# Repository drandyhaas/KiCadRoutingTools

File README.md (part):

# KiCad Routing Tools

A fast Rust-accelerated A* autorouter for KiCad PCB files. Compatible with **KiCad 9 and KiCad 10**. Available as both a **KiCad Plugin** with full GUI and a **Command-Line Interface** for scripting and automation.

📊 **[Project metrics](https://drandyhaas.github.io/KiCadRoutingTools/metrics/)** — installs, downloads and traffic, updated daily.

<p align="center">
  
  <br>
  Free and MIT-licensed. Donations cover the ~$500/month of cloud compute and AI development behind it.
  <br>
  Also via <a href="https://github.com/sponsors/drandyhaas">GitHub Sponsors</a> or <a href="https://www.paypal.me/DrAndyHaas">PayPal</a> — see <a href="#support">Support</a>.
</p>

## Contents

- [Support](#support) — donate via Ko-fi, GitHub Sponsors or PayPal
- [Features](#features)
- [Quick Start](#quick-start)
- [KiCad Plugin](#kicad-plugin) — GUI, the **Auto** tab (the Autorouter, AI routing and placement, labels), installation
- [Command-Line Interface](#command-line-interface) — routing, planes, verification
- [Documentation](#documentation) — full guide for every feature
- [Project Structure](#project-structure) & [Module Overview](#module-overview)
- [Performance](#performance)
- [Command Reference](#command-reference) — options per tool (full list: `--help` / [configuration.md](docs/configuration.md))
- [Project metrics](https://drandyhaas.github.io/KiCadRoutingTools/metrics/) — installs, downloads and traffic
- [Requirements](#requirements) · [Limitations](#limitations) · [Contributing](#contributing) · [License](#license)

## Support

KiCadRoutingTools is free and MIT-licensed, and it stays that way — there is no
paid tier, no feature held back, and nothing in this repository is paywalled.

Donations go to what it costs to build and maintain it: about **$500/month** of
cloud computing and AI-assisted development.

The compute is not incidental. Every change to the router is A/B-tested by
replaying a corpus of real open-source boards on rented cores and grading each
one for DRC violations and unconnected nets, and the ~770-file test suite fans
out the same way. It is what stops a change that helps one board from quietly
breaking ten others.

- **[☕ Donate on Ko-fi](https://ko-fi.com/drandyhaas)** — card or PayPal, no account needed.
- **[GitHub Sponsors](https://github.com/sponsors/drandyhaas)** — one-time or monthly, billed with any other projects you sponsor.
- Prefer PayPal directly? **[paypal.me/DrAndyHaas](https://www.paypal.me/DrAndyHaas)** (the sender needs a PayPal account).

A donation buys no priority support and unlocks no features. If you would rather
contribute something worth more than money, route one of your own boards and file
an issue for whatever breaks — see [Contributing](#contributing).

## Features

Fast, grid-based A\* routing with a native Rust core (~10× faster than pure Python): octilinear (H/V/45°) multi-layer routing with automatic vias, and batch routing with incremental obstacle caching. Highlights below link to the full deep-dive docs.

**Core routing**
- Rust-accelerated A\* pathfinding, multi-layer with automatic via insertion
- [Rip-up and reroute](docs/rip-up-reroute.md) — progressive N+1 blocker analysis, ripped-corridor avoidance
- [Net ordering strategies](docs/net-ordering.md) — MPS (crossing-aware), inside-out, original, or bus-first, with MPS layer swaps
- Stub layer switching, vertical track alignment, turn-cost straightening
- Board-edge (Edge.Cuts arcs/cutouts), keep-out rule areas, and auto BGA exclusion zones — see [Configuration](docs/configuration.md)
- Direction-aware stub / BGA / track [proximity penalties](docs/configuration.md)

**Differential pairs** — see [Differential Pairs](docs/differential-pairs.md)
- Pose-based A\* with a Dubins heuristic and adaptive setback angles for orientation-aware centerlines
- Bare-pad, multi-point (3+ terminals), and hybrid (coupled middle + single-ended legs) routing
- Automatic polarity resolution (opt-in pad swaps), U-turn prevention, GND return-via placement
- Electrically-short legs auto-defer to single-ended; per-layer [impedance-controlled](docs/differential-pairs.md) widths

**Power & planes** — see [Plane Routing](docs/route-plane.md) and [Power Nets](docs/power-nets.md)
- [Wider power-net routing](docs/power-nets.md) with automatic neck-down at fine-pitch pads
- Plane pours (pads are welded by the route step, #562) and plane layers several nets share (split round spines routed on the layer) with resistance / max-current reporting
- Disconnected-plane-region repair (region joins + pad taps) and GND return-via placement

**Signal integrity**
- [Length matching](docs/length-matching.md) — trombone meanders, auto DQ/DQS grouping, via-barrel aware
- [Time matching](docs/length-matching.md#time-matching) — propagation delay, microstrip vs stripline
- [Bus routing](docs/bus-routing.md), plus [guide corridors and keep-out zones](docs/configuration.md) drawn on a User layer

**Placement, fanout & optimization**
- [Placement by function](py_placer/placement/README.md): parts sorted into functional groups, one objective annealed (`place_simple.py`) over 12 seeds (6 started scattered, 6 with each group gathered), and a fast route (`route.py --quick 2`) of the 6 the objective rates best to keep the best (`/plan-pcb-placement`)
- [The design brief](docs/design-brief.md) — state what the board is FOR, in a sibling the toolchain reads: which connectors are user-facing, which edge each belongs on and where along it
- [Parts under other parts](docs/floorplan-intent.md#covers-and-heights-what-stands-over-the-board) — part heights read off the 3D models, so a low part may stand under a module or shield can where it fits; a card in its socket (M.2) or a module on a stacking connector is declared in the brief and moves with its connector, admitting only parts known to fit under it
- [Floorplan intent, graded](docs/floorplan-intent.md) — declare where parts belong and check the board against it, so "the render looks fine" stops being a verdict
- BGA / QFN fanout with decoupling-cap placement cleanup, Hungarian target-swap, and schematic sync

**Cleanup & verification** — see [Utilities](docs/utilities.md)
- Post-route copper cleanup reconciled against the connectivity model (no orphaned or ripped-and-not-restored copper), with gap-snap connectors
- **KiCad-oracle reconnect** — routes the exact links KiCad's own DRC reports as unconnected
- Checkers for DRC, connectivity, orphan stubs, copper hygiene (`check_weird.py`), and pad geometry

**Interfaces**
- Full [KiCad plugin GUI](#kicad-plugin) (KiCad 9 & 10) and a scriptable [CLI](#command-line-interface)
- [AI assistance](docs/claude-skills.md) — an **Auto** tab that runs the Autorouter, plans an entire routing workflow or places a board by function, per-field "Ask AI" helpers, and datasheet-driven power / high-speed / diff-pair analysis
- [Board rendering](docs/utilities.md#board-renderer-route_renderpy) — fast geometry PNG renderer (`route_render.py`), placement stills (`render_placement.py`), a board's power components (`render_power.py`), and movies of a routing run (`route_movie.py`, made for every stress run) and of a placement, or the placement skill's whole flow through to the full route (`place_movie.py`)
- [Routing plans as files](docs/claude-skills.md#plans-from-the-command-line) — save/load a whole routing chain as JSON: build one from a recorded command chain (`make_plan.py`), run it headless through the real plugin (`run_plan.py`), or load it in the GUI

## Quick Start

### 1. Get the Code

```bash
# Clone with git
git clone https://github.com/drandyhaas/KiCadRoutingTools.git
cd KiCadRoutingTools
```

Or [download the ZIP](https://github.com/drandyhaas/KiCadRoutingTools/archive/refs/heads/main.zip) and extract it.

Commands here use `python3`. On Windows, use `py -3` (or `python`) if `python3` is not found.

### 2. Install the Rust Router

```bash
python3 build_router.py
```

By default this downloads a prebuilt binary for your OS from the project's
[GitHub Releases](https://github.com/drandyhaas/KiCadRoutingTools/releases) —
**no Rust toolchain required**. Prebuilts are published for:

- Linux x86_64
- macOS arm64 (Apple Silicon)
- macOS x86_64 (Intel)
- Windows x86_64

If a prebuilt isn't available for your platform (e.g. Linux arm64) or the
download fails, the script falls back to building locally with cargo.

#### Building from source (optional)

If you'd rather build locally — or you're on a platform without a prebuilt —
install Rust from [rustup.rs](https://rustup.rs/):

```bash
# macOS / Linux
curl --proto '=https' --tlsv1.2 -sSf https://sh.rustup.rs | sh

# Windows: Download and run rustup-init.exe from https://rustup.rs/
```

After installation, restart your terminal or run `source ~/.cargo/env`, then:

```bash
python3 build_router.py --from-source     # build locally instead of downloading
python3 build_router.py --tag v0.15.0     # download a specific release
python3 build_router.py --clean           # remove all build artifacts
```

### 3. Choose Your Interface

**To route a whole board automatically, use one of two ways** -- and an AI assistant
asked to route a board with this package should do the same:

- `python3 py_router/autoroute.py board.kicad_pcb routed.kicad_pcb` (Option C): no
  agent; it plans the chain from the board's own rules, footprints and nets and runs it.
  The plugin's **Auto › Autorouter** tab runs the same script.
- the `/plan-pcb-routing` skill (Option B): an agent analyzes the board, plans the
  chain step by step with you, and runs it.

**Option A: KiCad Plugin (Recommended for interactive use)**

```bash
# Install the plugin
python3 install_plugin.py

# Then in KiCad: Tools → External Plugins → KiCadRoutingTools
```

**Option B: Claude Code (AI-assisted routing)**

Use [Claude Code](https://claude.ai/claude-code) to analyze your PCB and generate a routing plan:

```
> /plan-pcb-routing kicad_files/my_board.kicad_pcb
```

Claude will:
- Analyze your board structure and identify components needing fanout (BGA/QFN/PGA)
- Detect differential pairs and DDR signals requiring length matching
- Identify power/ground nets and recommend plane vs trace routing
- Assess signal speeds and recommend GND return via placement
- Generate a step-by-step routing plan with explanations
- Run the commands and verify results

Other useful skills:
```
> /find-high-speed-nets kicad_files/my_board.kicad_pcb       # Identify high-speed nets via datasheet lookup
> /analyze-power-nets kicad_files/my_board.kicad_pcb         # Identify power nets and track widths
> /identify-diff-pairs kicad_files/my_board.kicad_pcb        # Find diff pairs by pin function, recommend gap/impedance
> /recommend-stackup kicad_files/my_board.kicad_pcb          # Stackup advice for impedance/time-matching accuracy
> /recommend-plane-mappings kicad_files/my_board.kicad_pcb   # Which nets get planes, on which layers
> /diagnose-routing-failures my_board.kicad_pcb /tmp/route_output.txt  # Root-cause failed routes, get a retry command
> /review-routed-board my_board_routed.kicad_pcb             # Post-route QA: DRC, connectivity, length match, GND vias
> /plan-pcb-placement full kicad_files/my_board.kicad_pcb    # Group, place 12 seeds, fast-route the 6 cheapest, keep the best, route end to end
```

See [Claude Skills](docs/claude-skills.md) for what each skill does and how they fit together.

All of these are also available inside KiCad without leaving the plugin - see [AI assistance in the plugin](#ai-assistance-auto-tab) below. The plugin can run the analysis and routing skills through [opencode](https://opencode.ai) instead of Claude Code (issue #503) - a Backend dropdown on the Auto tab selects the agent CLI, and opencode's `provider/model` strings open the door to other model providers. The placement runs need Claude Code, because they write files and opencode's analysis agent may not. The skills' output contracts are tuned on Claude models; smaller models may follow them less reliably.

**Option C: Command Line -- route a whole board with `autoroute.py`**

```bash
# Route the whole board: planes, fanouts, decap clearance, diff pairs and route
# passes, chosen from the board's own rules, footprints and nets
python3 py_router/autoroute.py my_board.kicad_pcb routed.kicad_pcb

# See its plan first, without running anything
python3 py_router/autoroute.py my_board.kicad_pcb routed.kicad_pcb --dry-run
```

Every step it ran, with its log and board, is in `routed.kicad_pcb.autoroute/`
(`plan.json` there records the chain and each pass's grade), and its last line,
`AUTOROUTE_SUMMARY`, names the shipped step with its open nets and DRC. See
[`autoroute.py`](docs/utilities.md#deterministic-plan-router-autoroutepy). The
plugin's **Auto › Autorouter** tab runs the same script on the open board.

**Option D: A hand-built chain (the manual / expert path)**

When a board needs steps `autoroute.py` does not take -- impedance control, length
matching, keep-away rules, buses, a particular plane map, or a net class that is a
real requirement rather than aspirational -- run the tools yourself, the kind of chain
`/plan-pcb-routing` plans:

```bash
# Optionally place the board first, by its functional groups (see py_placer/placement/README.md)
python3 py_placer/place_simple.py my_board.kicad_pcb placed.kicad_pcb --groups groups.json --intent intent.json

# Pour the planes FIRST (#562): the fanout's plane-drop vias then land on
# real fill, and the route step welds plane pads into it.
python3 py_router/route_planes.py my_board.kicad_pcb poured.kicad_pcb --nets GND --plane-layers B.Cu

# Fan out a BGA, then tidy decoupling caps off the new vias (issue #130)
python3 py_router/bga_fanout.py poured.kicad_pcb -c U1 -o fanned.kicad_pcb --clearance 0.1
python3 py_placer/place_fanout_clearance.py fanned.kicad_pcb capclean.kicad_pcb --clearance 0.1

# Route differential pairs (the output is positional: route_diff's -o is --ordering)
python3 py_router/route_diff.py capclean.kicad_pcb diffed.kicad_pcb --nets "*lvds*"

# Route ALL remaining nets, plane nets included (their widths via --power-nets).
# This step ends with the in-run plane finalize that completes the planes.
python3 py_router/route.py diffed.kicad_pcb routed.kicad_pcb --nets "*" \
    --power-nets GND --power-nets-widths 0.3
```

---

## KiCad Plugin

The plugin provides a full graphical interface for all routing features, running directly within KiCad 9 or 10.

### AI assistance (Auto tab)

With [Claude Code](https://claude.ai/claude-code) or [opencode](https://opencode.ai) installed, the routing dialog gains AI assistance throughout (the plugin spawns the selected agent CLI headless, streams a live transcript, and fills GUI controls from the results). The **Backend** dropdown on the Auto tab picks the CLI: Claude Code runs Anthropic models; opencode takes `provider/model` strings for many providers (including its built-in free tier), with `opencode auth login` adding provider accounts. Both discover the same `.claude/skills/`; opencode runs them under a read-only `pcb-analysis` agent defined in `opencode.json` (the equivalent of the Claude run's read-only tool allowlist). Neither grants a dedicated write tool, though both grant `Bash`, so neither is a sandbox — the allowlist states intent, and `--allowedTools` auto-approves rather than restricts. Both can dispatch a subagent, so an analysis skill can hand its close-out to an independent verifier (#552): the Claude allowlist grants the dispatch tool per run, and the `pcb-analysis` agent grants opencode's `task` tool in `opencode.json`. A caller asking opencode for a tool set naming `Write`/`Edit` is refused rather than silently downgraded.

The tab has two sub-tabs:

- **Routing** - *Plan Routing* runs `/plan-pcb-routing`: the plan fills the parameter fields across the tabs and appears as a checkable step list, which *Run Selected Steps* executes sequentially in-process on the live board with per-step status marks. *Review Routed Board* and *Diagnose Routing Failures* give post-route QA and failure root-causing. Backend, model, and effort selectors control every AI run and persist with the dialog settings (model/effort remembered per backend).
- **Placement** - *Place (AI)* and *Place + Route (AI)* run `/plan-pcb-placement place` / `full` headless into a `krt_placement/` folder beside the board. The tab shows the seed candidates with a preview, a status line read from the run's milestone ledger, and at the end REPORT.md; *Apply Result to Board* moves the open board's parts to the result's poses and locks (and, after *Place + Route*, its routed copper). These two need Claude Code. *Beautify Labels* (no AI) tidies the reference-designator silkscreen (`py_placer/beautify_labels.py`).
- **Save / Load a plan** - *Save…* writes the generated step list to a JSON file; *Load…* reads one back and runs it with **no Claude call** — handy for replaying a workflow that worked on another board. A recorded command chain converts to a loadable plan too (`python3 py_router/make_plan.py <run dir>`; see [Plans from the command line](docs/claude-skills.md#plans-from-the-command-line)).
- **Per-field "Ask AI" buttons** - power nets/widths (Route tab), stackup check (Layers), differential-pair verification by pin function (Differential tab), net-to-plane layer mappings and GND return via distance (Planes tab).

The full button-to-skill map is in [Claude Skills - Plugin GUI Integration](docs/claude-skills.md#plugin-gui-integration). Datasheet-based skills use web lookups and take a few minutes; every run shows a live transcript with cancel.

### Installation

Three ways to install:

**A. KiCad Plugin and Content Manager (PCM)** — the recommended path for end users, and it needs no extra repository URL: the package has been in the **official KiCad repository** (the one KiCad ships with, `gitlab.com/kicad/addons`) since v0.15.6. Open the PCM from the KiCad main window, leave the repository dropdown on *KiCad official repository*, go to the **Plugins** tab, search for `routing`, select *KiCad Routing Tools* and click **Install**, then **Apply Changes** at the bottom. If it is not listed, the PCM is serving a cached catalogue — press **Refresh** and look again. Versions are published with status `testing` rather than `stable`, which the PCM shows in the Status column but does not hide or block; `kicad_version` is a *minimum*, so the 9.0 entry installs on KiCad 10 as well. On first launch, the plugin checks the Python packages listed in `requirements.txt` (`numpy`, `scipy`, `shapely`, and the optional `Pillow`, without which only board renders and the placement preview are off) and offers a one-click pip install for any that are missing **or too old** into KiCad's Python. Do not assume KiCad supplies them: what it bundles varies by version and platform, and KiCad 10 on macOS ships no `numpy` at all. The check reports the version and the file path the *running* interpreter imports — KiCad's Python is often not the one `pip show numpy` answers for in a terminal.

**B. PCM "Install from File…" using the release zip** — for a release newer than the one the official catalogue currently carries, for a pinned older version, or for an offline machine. Each [GitHub Release](https://github.com/drandyhaas/KiCadRoutingTools/releases) ships a ready-to-install PCM package zip named `KiCadRoutingTools-<version>.zip` (a single cross-platform archive bundling the prebuilt Rust binaries for all platforms — **not** the auto-generated "Source code (zip)"). To install it:

1. From the Release's *Assets*, download `KiCadRoutingTools-<version>.zip` (e.g. `KiCadRoutingTools-0.15.13.zip`).
2. In KiCad, open **Plugin and Content Manager** from the main window.
3. Click **Install from File…** (bottom of the PCM dialog) and select the downloaded zip.
4. Click **Apply Pending Changes**, then restart KiCad if prompted.

The plugin appears under *Tools → External Plugins* in the PCB Editor. The same first-launch `scipy`/`shapely` dependency check described in (A) applies. This path keeps the plugin manageable from the PCM (you can update or uninstall it there), unlike the manual install below.

**C. Manual install from source** — for development or for using the CLI tools as well:

```bash
# Install the plugin (copies to KiCad plugins directory)
python3 install_plugin.py

# For development: create symlink instead of copying
python3 install_plugin.py --symlink

# Remove the plugin
python3 install_plugin.py --uninstall

# Skip installing the Python dependencies
python3 install_plugin.py --no-deps
```

The installer installs into every KiCad version it finds (version directories and install roots are discovered, not taken from a fixed list), under:
- **macOS**: `~/Documents/KiCad/<version>/3rdparty/plugins/`
- **Linux**: `~/.local/share/kicad/<version>/3rdparty/plugins/`
- **Windows**: `~/Documents/KiCad/<version>/3rdparty/plugins/`

The installer also installs `requirements.txt` into KiCad's Python with pip, and skips pip when that Python already has everything. On Linux, KiCad runs the system Python, which Debian 12+, Ubuntu 23.04+, Fedora 38+ and Arch mark as externally managed (PEP 668) so pip refuses to install into it; there the installer runs no pip and prints the `apt` / `dnf` / `pacman` command for whatever is missing, plus the explicit `--break-system-packages` override for a package your distribution does not carry.

If you previously installed this plugin through the Plugin & Content Manager, that copy sits next to the local install and would shadow it on `sys.path` (causing stale-code errors). The installer detects any such PCM copy and moves it aside to `<kicad-base>/disabled_pcm_plugins/<version>/`, leaving it recoverable. Pass `--keep-pcm` to skip this.

### Releasing a new version (maintainers)

The full release flow — version bump, GitHub Release, and the merge request to the official KiCad PCM repository — is documented step by step in **[docs/release-pipeline.md](docs/release-pipeline.md)**.

Short version:

1. Bump `VERSION` and the `versions[]` entry in `metadata.json` (and `rust_router/Cargo.toml` only when the Rust crate changed); `python3 check_release_version.py --tag vX.Y.Z` checks they agree.
2. `git tag v0.15.6 && git push --tags` — CI builds all 4 platform binaries, packages a single `KiCadRoutingTools-<ver>.zip` (the PCM validator rejects duplicate version strings, so we ship one cross-platform zip), patches `metadata.json` with real sha256/size values, and attaches everything to the GitHub Release.
3. Append the new version to the metadata file in your fork of `gitlab.com/kicad/addons/metadata` and open an MR. See the docs page for the exact commands.

To build a zip locally for testing:

```bash
python3 package_pcm.py --binary-dir ./path/to/release/artifacts
```

### Usage

1. Open KiCad (9.0 or later)
2. Open a PCB in Pcbnew
3. *(Optional)* Select one or more nets in the PCB editor first — for example by
   clicking tracks/pads, or right-clicking a track and choosing
   **Select → All Tracks in Net**. Any nets you have selected are automatically
   pre-checked for routing when the plugin opens.
4. Go to **Tools → External Plugins → KiCadRoutingTools**
5. To route the whole board hands-off: **Auto › Autorouter ›
   Run Autorouter**, review its steps, then **Apply Result to Board**
6. Or, by hand: configure routing parameters, select (or adjust) the nets to route,
   and click **Route** on the Route tab

### Plugin Tabs

**Auto Tab** (the first tab; a fresh dialog opens on it, a reopened one on the page it was closed on):
- *Autorouter* sub-tab: route the whole board with no agent. **Run Autorouter** runs
  [`autoroute.py`](docs/utilities.md#deterministic-plan-router-autoroutepy) as a
  subprocess on a snapshot of the open board (with its `.kicad_pro` / `.kicad_dru`),
  in a temp work folder. Its **Plan** pane shows what it read off the board -- the
  design rules and where they came from, the planes, the parts it fans out and the
  ones it does not, with why, the diff pairs and power nets -- and its **Steps**
  checklist one row per step, pending / running (time ticking) / done / FAILED /
  skipped, with each step's result (escapes and grazes, caps moved, pairs routed,
  each route pass's open nets and DRC, which pass shipped, why a pass did not run);
  the rows the run adds (a fanout's next rung, a re-fan) appear as they start.
  Selecting a row shows its command line, decisions, summary and log tail (a failed
  one its exit code and error). Options: *Finish only* (`--finish`), *Effort factor*
  (`--effort-factor`), *Plane layer cost* (`--plane-layer-cost`). **Stop** kills the
  run and its steps. **Apply Result to Board** makes the open board match the shipped
  result -- footprint poses (the decap step moves caps), tracks and vias (live copper
  the result does not have is removed), the zones with their fills (not refilled), and
  the design rules the result was graded against -- after listing every change.
- *AI Routing* sub-tab: plan a routing chain with `/plan-pcb-routing` and run its steps; review and diagnose; save/load plans (see [AI assistance](#ai-assistance-auto-tab) above)
- *AI Placement* sub-tab: place (and route) the board with `/plan-pcb-placement`
- *Labels* sub-tab: Beautify Labels -- uniform, non-overlapping reference-designator silkscreen, the CLI's `py_placer/beautify_labels.py`

**Route Tab:**
- Net selection with filtering and component filtering
- Nets selected in the PCB editor before opening the plugin are pre-checked automatically (also applies to the Fanout, Planes, and Differential tabs)
- Option to separate nets by net class (organizes into tabs per class)
- Track width, clearance, via size/drill from net class or manual override; impedance; the fab tier, escalation policy and clearance ceiling (the CLI's `--fab-tier`, `--escalation`, `--clearance-ceiling`)
- Layer selection with per-layer cost multipliers
- Options: stub layer swaps, copper text moving, teardrops, DRC-settings fix, power net widths and neck-down, no-BGA zones, smoothing
- **Guide corridor** - draw a polyline on a User layer (e.g. `User.1`) and tick "Follow User-layer guide path" to route the selected nets along it (waypoints, avoiding obstacles, packed non-overlapping)
- **Keepout zones** - draw one or more closed polygons on a User layer (e.g. `User.2`) and tick "Keep out of User-layer polygon(s)" to keep routed tracks out of those areas (hard keepout, all routed nets)
- **Clear guide/keepout layers** - optional "Clear guide layer after routing" / "Clear keepout layer after routing" checkboxes (unchecked by default) delete the drawn guide/keepout graphics from their User layer after a successful route, so you can draw fresh ones for the next run

**Advanced Tab:**
- Swappable nets configuration for target swap optimization
- Routing parameters: iterations, heuristic weight, rip-up, probe iterations
- MPS ordering options, direction control, length matching
- Proximity settings: BGA, stub, track, via proximity costs
- Debug options

**Differential Tab:**
- Differential pair selection with filtering
- Pair width and gap, differential impedance, turning radius, setback angle configuration
- Options: polarity fix, GND vias, intra-pair length matching, AC-coupled end-to-end matching
- **Ask AI** confirms pairs by pin function

**Fanout Tab:**
- BGA fanout with exit margin, escape direction, differential pair support, and plane-net ball drops
- Escape method: auto (channel router, under-pad retry), channel, under-pad for dense fully-populated BGAs (issue #122), or dog-bone — see [BGA Fanout](py_router/bga_fanout/README.md#escape-methods)
- "Optimize decoupling cap placement" option (off by default) — after fanout, nudges decoupling caps off foreign-net fanout vias and toward same-net balls — see [Decap Clearance Repair](docs/utilities.md#decap-clearance-repair-place_fanout_clearancepy)
- QFN fanout with extension length, escape layer, and an under-pad (via-drop) escape
- Net selection for fanout operations

**Planes Tab** (pour creation only since #562 — plane repair runs inside
every route, and the route step welds plane pads into the pour):
- Net-to-layer assignment for power/ground planes (**Ask AI** recommends one)
- Create the pours (plus thermal via arrays under exposed pads, optional thermal-relief connections)
- Area via stitching, a board-edge via fence, and GND return via placement near signal vias
- Via size/drill, zone clearance configuration

**Log Tab:**
- Real-time routing output display
- Color-coded messages (errors, warnings, success)

**About Tab:**
- Version information and credits
- Window transparency, *Validate PCB Data* (the pcbnew-built board model against the file parser's, reported in the Log tab) and *Reset All Settings to Defaults*

**General Features:**
- Settings persistence (parameters and selections preserved between sessions)
- Cancel button to stop routing operations mid-progress
- Results applied directly to the open PCB in KiCad

---

## Command-Line Interface

### Net Pattern Syntax

All `--nets` options support fnmatch-style wildcards and exclusion patterns:

| Pattern | Description |
|---------|-------------|
| `*` | All nets |
| `*DATA*` | Nets containing "DATA" |
| `/*` | Nets starting with "/" (hierarchical) |
| `Net-(U1-*)` | Nets matching "Net-(U1-...)" |
| `!GND` | Exclude net named "GND" |
| `!*VCC*` | Exclude nets containing "VCC" |
| `"*" "!GND" "!VCC"` | All nets except GND and VCC |

**Notes:**
- Exclusion patterns (starting with `!`) remove matching nets from the result
- Order matters: include patterns add nets, exclude patterns remove them
- Nets starting with "unconnected-" are automatically excluded
- Use quotes around patterns with special characters

### Route a Whole Board

`autoroute.py` routes a whole board with no agent (the other way is the
`/plan-pcb-routing` skill): it reads the board's rules, footprints and nets, plans the
chain (planes, fanouts, decap clearance, diff pairs, route passes) and runs it, each
step as its own process. The commands below are the tools it runs, for a hand-built
chain.

```bash
python3 py_router/autoroute.py kicad_files/input.kicad_pcb kicad_files/output.kicad_pcb
python3 py_router/autoroute.py kicad_files/input.kicad_pcb kicad_files/output.kicad_pcb --dry-run
```

### Route Nets

```bash
# Route all nets (default) - outputs to input_routed.kicad_pcb
python3 py_router/route.py kicad_files/input.kicad_pcb

# Route all nets, overwrite input file
python3 py_router/route.py kicad_files/input.kicad_pcb --overwrite

# Route all nets to a specific output file
python3 py_router/route.py kicad_files/input.kicad_pcb kicad_files/output.kicad_pcb

# Route specific nets (using --nets option)
python3 py_router/route.py kicad_files/input.kicad_pcb kicad_files/output.kicad_pcb --nets "Net-(U2A-DATA_0)" "Net-(U2A-DATA_1)"

# Route with wildcard patterns
python3 py_router/route.py kicad_files/input.kicad_pcb kicad_files/output.kicad_pcb --nets "Net-(U2A-DATA_*)"

# Route all nets on a component (auto-excludes GND/VCC/VDD/unconnected)
python3 py_router/route.py kicad_files/input.kicad_pcb kicad_files/output.kicad_pcb --component U1

# Route specific patterns on a component (no auto-exclusion)
python3 py_router/route.py kicad_files/input.kicad_pcb kicad_files/output.kicad_pcb --nets "/DDAT*" --component U1

# Route ALL nets on a component including power (use "*" pattern)
python3 py_router/route.py kicad_files/input.kicad_pcb kicad_files/output.kicad_pcb --nets "*" --component U1

# Exclusion-pattern SYNTAX demo (! prefix). NOTE: in the #562 chain you do
# NOT exclude plane nets from the route step -- see the chain example below.
python3 py_router/route.py kicad_files/input.kicad_pcb kicad_files/output.kicad_pcb --nets "*" "!GND" "!VCC"

# Route one placement BLOCK -- a schematic sheet, a KiCad group, a net-name prefix, an IC and
# its decaps (--group-by kicad,sheet,netprefix,decap; auto = kicad,sheet; --list-groups shows them)
python3 py_router/route.py kicad_files/input.kicad_pcb kicad_files/output.kicad_pcb \
  --group-by sheet --list-groups                      # what blocks exist?
python3 py_router/route.py kicad_files/input.kicad_pcb kicad_files/output.kicad_pcb \
  --group sheet:558c3023 --group-by sheet --group-scope internal

# PREVIEW any routing run: route it, report what it WOULD add, write no board
python3 py_router/route.py kicad_files/input.kicad_pcb kicad_files/output.kicad_pcb \
  --group sheet:558c3023 --group-by sheet --preview --preview-png preview.png

# UNDO: strip the scoped nets' copper back to unrouted (needs an explicit scope;
# defaults to --group-scope internal, since a block's "touching" nets include
# GND/VCC and undoing those would strip their copper across the whole board)
python3 py_router/route.py kicad_files/input.kicad_pcb kicad_files/undone.kicad_pcb \
  --group sheet:558c3023 --group-by sheet --undo

# Route differential pairs (use route_diff.py)
python3 py_router/route_diff.py kicad_files/input.kicad_pcb kicad_files/output.kicad_pcb --nets "*lvds*" --no-bga-zones

# Route with wider tracks for power nets
python3 py_router/route.py kicad_files/input.kicad_pcb kicad_files/output.kicad_pcb --nets "Net*" \
  --power-nets "*GND*" "*VCC*" "+3.3V" --power-nets-widths 0.4 0.5 0.3 --track-width 0.2

# Typical workflow: create GND plane first, then route all signals
python3 py_router/route_planes.py kicad_files/flat_hierarchy.kicad_pcb --nets GND --plane-layers B.Cu
python3 py_router/route.py kicad_files/flat_hierarchy_routed.kicad_pcb --overwrite
```

### Create Power/Ground Planes

```bash
# Pour a GND zone on B.Cu (outputs to input_routed.kicad_pcb). The pour places no
# per-pad taps: the route step that follows welds the plane pads into it (#562)
python3 py_router/route_planes.py kicad_files/input.kicad_pcb --nets GND --plane-layers B.Cu

# Create GND zone, overwrite input file
python3 py_router/route_planes.py kicad_files/input.kicad_pcb --overwrite --nets GND --plane-layers B.Cu

# Create GND zone to specific output file
python3 py_router/route_planes.py kicad_files/input.kicad_pcb kicad_files/output.kicad_pcb --nets GND --plane-layers B.Cu

# Create multiple planes at once (each net paired with corresponding plane layer)
python3 py_router/route_planes.py kicad_files/input.kicad_pcb --nets GND +3.3V --plane-layers In1.Cu In2.Cu

# VCC plane; --via-size/--via-drill size this step's own vias (thermal arrays, stitching)
python3 py_router/route_planes.py kicad_files/input.kicad_pcb --nets VCC --plane-layers In2.Cu --via-size 0.5 --via-drill 0.4

# Multiple nets sharing one layer, split round spines routed on it (use | separator)
python3 py_router/route_planes.py kicad_files/input.kicad_pcb --nets GND "VA19|VA11" --plane-layers In4.Cu In5.Cu

# Dry run to see what would be placed
python3 py_router/route_planes.py kicad_files/input.kicad_pcb --nets GND --plane-layers B.Cu --dry-run
```

GND return vias (`--add-gnd-vias`) and area stitching (`--stitch-vias`, `--stitch-edge-fence`) go in a re-run of the same pour after routing, so they place around the finished signals, and a return via needs GND poured on two layers — see [Plane Routing](docs/route-plane.md).

### Repair Disconnected Plane Regions

> **Since #562 you normally do not run this step.** Every `route.py` run
> finishes with an in-run *plane finalize* that applies this same engine
> (pad taps + region joins), the plane-copper cleanup, and a KiCad-oracle
> completion check — so a pours-first chain repairs its planes automatically.
> `KICAD_PLANE_FINALIZE=0` is the kill switch. The finalize runs even when
> the route step finds nothing else to route (#1112), so a chain should end
> on `route.py`, never on this script. Use the standalone script below for a
> board routed OUTSIDE that chain (e.g. hand-edited copper); its track and
> via default to the board's Default net class, not to the sizes a chain
> routed at, so pass `--track-width` / `--via-size` / `--via-drill` if they
> differ.

After creating power planes, regions may become split by vias and traces from other nets. Use `repair_planes.py` to reconnect them:

```bash
# Auto-detect all zones in PCB and repair disconnected regions (outputs to input_routed.kicad_pcb)
python3 py_router/repair_planes.py kicad_files/input.kicad_pcb

# Auto-detect all zones, overwrite input
python3 py_router/repair_planes.py kicad_files/input.kicad_pcb --overwrite

# Auto-detect all zones to specific output file
python3 py_router/repair_planes.py kicad_files/input.kicad_pcb kicad_files/output.kicad_pcb

# Specific nets and layers
python3 py_router/repair_planes.py kicad_files/input.kicad_pcb --nets GND --plane-layers B.Cu

# Customize track width and clearance
python3 py_router/repair_planes.py kicad_files/input.kicad_pcb kicad_files/output.kicad_pcb \
    --track-width 0.5 --clearance 0.2
```

### Review a Placement

Placement deltas are invisible in a board file; render them instead.

```bash
# what moved, and did it help? (ghosts at the seed poses, arrows, metrics caption)
python3 py_tools/render_placement.py placed.kicad_pcb --before seed.kicad_pcb -o delta.png

# zoom to one placement block; same block names as route.py --group
python3 py_tools/render_placement.py board.kicad_pcb --list-groups --group-by sheet
python3 py_tools/render_placement.py board.kicad_pcb --zoom-group sheet:58d913ec --per-side -o out/

# everything a placement author reads, in one artifact: escape lanes, groups, and
# lock advice (which parts should NOT move) -- locks nothing, writes no board
python3 py_tools/board_brief.py board.kicad_pcb
```

Toggles for `--borders` / `--labels` / `--ratsnest` / `--arrows` / `--ghosts`;
`--per-side` gives F and B panels rather than one flattened projection.
The render is triage, and so are the caption's `crossings` / `hpwl`: a
placement is judged by routing it.

### Verify Results

```bash
# Check for DRC violations. With no -c, grades at the Default net-class clearance
# the routing steps wrote into the sibling .kicad_pro (the clearance the board was
# routed to), plus the board's .kicad_dru layer rules; falls back to 0.2mm if
# there's no project. Pass -c to override.
python3 py_router/check_drc.py kicad_files/output.kicad_pcb

# Cross-check with KiCad's own DRC engine (requires KiCad; --refill-zones avoids
# bogus zone-clearance errors from stale pours - see tests/README.md for details)
kicad-cli pcb drc --refill-zones --format json -o drc.json kicad_files/output.kicad_pcb

# ...because a routed board ships zone OUTLINES with no filled_polygon, so an
# unrefilled grade reports plane opens that are not real (#910). To ship a
# board that already carries its fills, add --write-fill to the route step, or:
python3 py_tools/fill_for_delivery.py kicad_files/output.kicad_pcb -o delivered.kicad_pcb

# Check connectivity (detects unrouted nets, broken routes, and T-junctions)
python3 py_router/check_connected.py kicad_files/output.kicad_pcb

# Check connectivity for specific nets
python3 py_router/check_connected.py kicad_files/output.kicad_pcb --nets "*DATA*"

# Check connectivity for all nets on a component
python3 py_router/check_connected.py kicad_files/output.kicad_pcb --component U1

# Only check routed nets (skip unrouted net detection)
python3 py_router/check_connected.py kicad_files/output.kicad_pcb --routed-only

# Check for orphan stubs (dead-end traces with no pad/via/trace at the loose end).
# Connection is judged by actual copper extent (via radius, pad size, trace
# half-width), so T-junction taps and copper-overlap joints are not miscounted.
python3 py_tools/check_orphan_stubs.py kicad_files/output.kicad_pcb

# Other-net copper inside the screw-head ring of each mounting hole (KiCad checks
# a hole's clearance only). Declare the ring before routing with
# add_rule_area.py --name MOUNT --mounting-holes. --ring MM sets how far past the
# hole edge the head reaches (default 0.4 x the drill).
python3 py_tools/check_mounting_holes.py kicad_files/output.kicad_pcb --ring 1.3

# Pad-geometry sanity check: flags same-footprint, different-net pads whose copper
# overlaps (a short). A non-zero result almost always means a pad's rotation/size
# is modelled wrong - the usual cause is a QFN/QFP/BGA placed at a non-orthogonal
# angle. The fanout tools run this automatically on their component first; run it
# yourself before fanout (or board-wide) as a standalone check:
python3 py_router/check_pads.py kicad_files/board.kicad_pcb                 # whole board, per footprint
python3 py_router/check_pads.py kicad_files/board.kicad_pcb --component U23 # one footprint
python3 py_router/check_pads.py kicad_files/board.kicad_pcb --cross-footprint  # also across parts

# Flag long non-orthonormal tracks. An on-grid router emits only 0/45/90-degree
# segments; the only legitimate non-orthonormal segment is a short (<=1 grid cell)
# terminal connector to an off-grid pad/ball. Anything longer is a routing defect
# (it can cut diagonally across foreign copper). qfn_fanout escape stubs are
# excluded automatically; bga_fanout's short stub-end jogs clear the 0.25mm default.
python3 py_tools/check_orthonormal.py kicad_files/output.kicad_pcb

# Copper hygiene (read-only): dangling stubs, same-net soft joints, redundant
# cycles, and removable / stacked / floating copper the routing left behind.
python3 py_router/check_weird.py kicad_files/output.kicad_pcb

# Is the board DONE? One verdict over board_score and the checkers above, which
# fails closed: exit 0 done, 4 incomplete, 5 graded clean only against floors
# the routing lowered (--authored-from names the board the chain started from)
python3 check_complete.py kicad_files/output.kicad_pcb --authored-from kicad_files/input.kicad_pcb
```

See [Utilities](docs/utilities.md) for every checker and its options, and
`python3 krt_registry.py` for every runnable tool in the clone with its purpose.

### Power Net Analysis

Use the `/analyze-power-nets` skill to identify power nets and get track width recommendations:

```
# Ask the AI to analyze your board with datasheet lookup
/analyze-power-nets kicad_files/my_board.kicad_pcb
```

The skill:
1. Auto-classifies obvious components (resistors, capacitors, inductors, etc.)
2. Uses WebSearch to look up datasheets for unknown components (ICs, connectors, transistors)
3. Classifies each component's role (power source, current sink, pass-through, shunt)
4. Traces power paths from sinks to sources
5. Generates ready-to-use `--power-nets` configurations

See [Power Net Analysis](docs/power-nets.md) for detailed documentation.

### High-Speed Net Analysis

Use the `/find-high-speed-nets` skill to identify high-speed nets and get GND return via recommendations:

```
# Ask the AI to analyze signal speeds with datasheet lookup
/find-high-speed-nets kicad_files/my_board.kicad_pcb
```

The skill:
1. Pre-classifies nets by name patterns (DDR, USB, SPI, CLK, etc.)
2. Pre-classifies components by footprint (FPGA, DDR, PHY, etc.)
3. Uses WebSearch to look up datasheets for ICs and extract max clock rates and rise times
4. Traces high-speed signals through series passives (termination resistors, AC coupling caps)
5. Generates a speed classification (ultra-high/high/medium/low) with recommended `--gnd-via-distance`

The `/plan-pcb-routing` skill includes a lightweight version of this analysis (net name and
footprint pattern matching only, no datasheet lookup) and automatically includes a GND return
via step when GND planes are present. Run `/find-high-speed-nets` first for more accurate
recommendations based on actual component specifications.

### Integration Tests

```bash
# Run full integration test (fanout + routing + checks)
python3 tests/test_fanout_and_route.py --all

# Quick mode for faster testing
python3 tests/test_fanout_and_route.py --all --quick

# The whole suite (~770 files, about 40 minutes on one machine when last measured)
python3 tests/run_all.py
```

See [tests/README.md](tests/README.md) for detailed documentation of all test scripts.

## Documentation

| Document | Description |
|----------|-------------|
| [Routing Architecture](docs/routing-architecture.md) | Module structure, obstacle maps, A* algorithm |
| [Python API](docs/python-api.md) | Using the modules as a library: parser, writer, modification, config, net analysis, impedance — with runnable examples |
| [Configuration](docs/configuration.md) | Command-line options, GridRouteConfig parameters |
| [Differential Pairs](docs/differential-pairs.md) | P/N pairing, polarity swaps, via handling |
| [Net Ordering](docs/net-ordering.md) | MPS algorithm, inside-out ordering, strategy comparison |
| [Rip-Up and Reroute](docs/rip-up-reroute.md) | Blocking analysis, progressive N+1 escalation, reroute loop |
| [Length Matching](docs/length-matching.md) | Trombone meanders, via barrel lengths, DDR auto-grouping, time matching |
| [Bus Routing](docs/bus-routing.md) | Bus detection and filter, corridor planning, middle-out ordering, corridor attraction; the topo bus step |
| [Guide Corridor](docs/configuration.md#guide-corridor-options-preferred-route) | User-layer guide paths, waypoints, best-effort following |
| [Power/Ground Planes](docs/route-plane.md) | Copper zones with automatic via placement |
| [Utilities](docs/utilities.md) | Every checker (DRC, connectivity, completion, hygiene, pads), the fanout generators, placement tools, renderers, the DRC-settings fixer |
| [Design Brief](docs/design-brief.md) | Declare what the board IS -- the facts a board file cannot contain -- and compile them into the intent (`<board>.design-brief.json`) |
| [Floorplan Intent](docs/floorplan-intent.md) | Declare the floorplan, grade the board against it (`check_floorplan.py`) |
| [BGA Fanout](py_router/bga_fanout/README.md) | BGA escape routing generator |
| [QFN Fanout](py_router/qfn_fanout/README.md) | QFN/QFP escape routing generator |
| [Rust Router](rust_router/README.md) | Building and using the Rust A* module |
| [Power Net Analysis](docs/power-nets.md) | Power net detection, AI analysis, track width guidelines |
| [Claude Skills](docs/claude-skills.md) | All ten AI skills: placement and routing end to end, routing plans, power/high-speed/diff-pair analysis, stackup, plane mappings, failure diagnosis, board review |
| [Placement](py_placer/placement/README.md) | Placement by function: groups, one annealed objective, legality, the floorplan intent's grade |
| [Integration Tests](tests/README.md) | Test scripts and performance benchmarks |
| [Release Pipeline](docs/release-pipeline.md) | How to tag a release and submit it to the KiCad PCM (maintainers) |

## Project Structure

```
KiCadRoutingTools/
├── py_router/                # Routing engine + CLI entry points (~130 modules)
│   ├── route.py                  # Main CLI - single-ended routing (ends with the in-run plane finalize, #562)
│   ├── route_diff.py             # Main CLI - differential pair routing
│   ├── route_planes.py           # Main CLI - power/ground plane pours
│   ├── repair_planes.py          # Standalone utility - repair disconnected plane regions (the chain step is absorbed into route.py's finalize, #562)
│   ├── route_render.py           # PNG still of a board from its geometry
│   ├── route_movie.py            # Movie of a routing run, step by step (route_trace.py records the router's events)
│   ├── make_plan.py              # Recorded command chain -> GUI routing plan (plan.json)
│   ├── run_plan.py               # Run a GUI routing plan headless, through the real plugin dialog
│   ├── autoroute.py              # Build a routing chain from the board itself and run it, no agent
│   ├── add_rule_area.py          # Write a copper keep-out rule area onto a board
│   ├── plane_io.py               # Plane I/O utilities (zone extraction, output writing)
│   ├── plane_obstacle_builder.py # Obstacle map building for plane via placement
│   ├── plane_blocker_detection.py # Blocker detection and rip-up for plane vias
│   ├── plane_zone_geometry.py    # Voronoi cells for a shared plane layer's split
│   ├── plane_split_raster.py     # Raster finishing of a shared plane layer's split
│   ├── plane_resistance.py       # Plane resistance and current capacity calculations
│   ├── plane_region_connector.py # Detect and route between disconnected plane regions
│   ├── routing_config.py         # GridRouteConfig, GridCoord, DiffPairNet classes
│   ├── routing_defaults.py       # Default routing parameter values
│   ├── routing_state.py          # RoutingState class - tracks routing progress
│   ├── routing_common.py         # Shared utilities for route.py and route_diff.py
│   ├── obstacle_map.py           # Obstacle map building functions
│   ├── obstacle_cache.py         # Net obstacle caching for incremental builds
│   ├── diff_pair_loop.py         # Differential pair routing loop
│   ├── single_ended_loop.py      # Single-ended routing loop
│   ├── reroute_loop.py           # Reroute queue processing
│   ├── diff_pair_routing.py      # Diff pair A* routing implementation
│   ├── single_ended_routing.py   # Single-ended A* routing implementation
│   ├── net_ordering.py           # MPS, inside-out, and original ordering
│   ├── rip_up_reroute.py         # Rip-up and reroute logic
│   ├── length_matching.py        # Length matching with trombone meanders
│   ├── kicad_parser.py           # KiCad .kicad_pcb file parser
│   ├── kicad_writer.py           # KiCad S-expression generator
│   ├── output_writer.py          # Route output and swap application
│   ├── pcb_modification.py       # Add/remove routes from PCB data
│   ├── impedance.py              # Impedance calculation (microstrip/stripline formulas)
│   ├── check_drc.py              # DRC violation checker
│   ├── check_connected.py        # Connectivity checker (with T-junction detection)
│   ├── check_pads.py             # Pad-geometry sanity checker
│   ├── check_weird.py            # Copper hygiene checker
│   ├── cleanup_pipeline.py       # The one ordered post-route cleanup pipeline (both routing fronts)
│   ├── fix_kicad_drc_settings.py # Make .kicad_pro DRC constraints consistent with the routed floors
│   ├── copy_board.py             # Copy a board WITH its sibling .kicad_pro/.kicad_dru
│   ├── list_nets.py              # List nets on a component
│   ├── startup_checks.py         # Startup checks (Python deps, Rust library version)
│   ├── bga_fanout.py             # BGA fanout CLI wrapper
│   ├── bga_fanout/               # BGA fanout package (escape, reroute, layer balance, under-pad escape, ...)
│   ├── qfn_fanout.py             # QFN/QFP fanout CLI wrapper
│   ├── qfn_fanout/               # QFN/QFP fanout package (layout, geometry, types)
│   └── ...                       # plus the rest of the engine modules — see Module Overview below
│
├── py_placer/                # Placement CLIs and the placement package
│   ├── place_simple.py           # The placer: functional groups, one objective, annealed
│   ├── place_movie.py            # place_simple with a camera: a movie of the placement, step by step
│   ├── judge_seeds.py            # The seed judge: judge.json's seeds routed by one quick chain, scored
│   ├── place_pose.py             # Set, turn, face, lock or replicate parts by hand
│   ├── place_fanout_clearance.py # Move decoupling caps off fanout vias
│   ├── beautify_labels.py        # Tidy the reference-designator silkscreen
│   ├── converge.py               # The milestone ledger: record, where, verdict
│   ├── placement/                # Component placement package — see py_placer/placement/README.md
│   │   ├── simple.py             # The placer's cost model
│   │   ├── simple_anneal.py      # The placer's simulated annealing
│   │   ├── quench.py             # QuenchState: the parts, their poses and the board
│   │   ├── grouping.py           # The groups file
│   │   ├── legality.py           # Placement legality checks
│   │   ├── floorplan.py          # Floorplan intent and its grade
│   │   ├── body.py               # THE footprint body model (#896)
│   │   ├── fanout_clearance.py   # Fanout clearance evaluation
│   │   ├── parser.py             # Courtyard boundary extraction
│   │   ├── writer.py             # Footprint position modification
│   │   └── ...
│   └── ...
│
├── py_tools/                 # Leaf diagnostic / analysis tools
│   ├── check_impedance.py        # Verify impedance-controlled widths/gaps
│   ├── check_orphan_stubs.py     # Orphan stub detector
│   ├── check_mounting_holes.py   # Other-net copper under a mounting hole's screw head
│   ├── check_cycles.py           # Redundant-loop (cycle) + overlapping-via checker
│   ├── check_orthonormal.py      # Long non-orthonormal track detector
│   ├── net_forensics.py          # Per-net copper forensics
│   ├── kicad_unconnected.py      # Unconnected-item listing
│   ├── validate_pcb_data.py      # PCBData validation
│   ├── extract_pcb_geometry.py   # Geometry extraction
│   ├── clean_ignored.py          # List / delete git-ignored files
│   ├── analyze_power_paths.py    # Power-path analysis (backs /analyze-power-nets)
│   ├── board_brief.py            # What a board looks like to whatever places it
│   ├── board_context.py          # Every part's value, pins, nets and role
│   ├── check_groups.py           # Check a groups file against its board
│   ├── check_floorplan.py        # Grade a board against its floorplan intent
│   ├── check_assembly.py         # Is a placement buildable?
│   ├── render_placement.py       # PNG stills of a placement, with its legality
│   ├── route_review.py           # What to move after a route
│   ├── render_nets.py            # Chosen nets' copper on several boards side by side
│   ├── render_power.py           # A board's power components over its rails
│   ├── board_score.py            # One score for a board: blocking, then quality
│   ├── quick_score.py            # Score a route.py --quick 2 board (the placement seed judge)
│   ├── check_reachability.py     # Is this pad reachable, or is the geometry to blame?
│   ├── check_join.py             # Verify a hand-drawn join against all board copper before committing it
│   ├── fill_for_delivery.py      # Write a filled copy of a routed board (#910)
│   └── _path.py                  # sys.path bootstrap so the tools import py_router
│
├── tests/                    # Tests (~770 files) and the stress/A-B harness
│   ├── run_all.py                # The whole suite (tests/stress/modal_suite/ fans it out onto Modal)
│   ├── test_fanout_and_route.py  # Full integration test (fanout + route)
│   ├── test_kit_route.py         # Pad-to-pad routing test (no fanout)
│   ├── test_flat_hierarchy.py    # 2-layer board with GND plane test
│   ├── test_interf_u.py          # 2-layer board with non-rectangular outline test
│   ├── test_sonde_u.py           # Wide track routing test
│   ├── run_utils.py              # Shared test utilities
│   ├── gui_parity/               # CLI/GUI parity gates — see tests/gui_parity/README.md
│   └── stress/                   # Real-world-board stress-test harness (run_queue.sh) — see tests/README.md
│
├── rust_router/              # Rust A* implementation
├── kicad_routing_plugin/     # KiCad ActionPlugin
│   ├── action_plugin.py      # ActionPlugin entry point
│   ├── swig_gui.py           # Main routing dialog (Route/Advanced tabs)
│   ├── differential_gui.py   # Differential pair routing tab
│   ├── fanout_gui.py         # BGA/QFN fanout tab and net selection panel
│   ├── planes_gui.py         # Power/ground planes tab
│   ├── tab_names.py          # The dialog's page and sub-tab names, in order
│   ├── autoroute_gui.py      # Auto tab, Autorouter sub-tab (runs autoroute.py on a snapshot, shows its steps)
│   ├── result_apply.py       # Apply Result to Board: poses, tracks/vias, zones, rules from a result file
│   ├── ai_gui.py             # Auto tab, AI Routing sub-tab (spawns the agent CLI headless, streams transcript)
│   ├── ai_plan.py            # Routing plans: parse, fill the tabs, run the steps (PlanExecutor)
│   ├── placement_gui.py      # Auto tab, AI Placement sub-tab
│   ├── labels_gui.py         # Auto tab, Labels sub-tab (Beautify Labels)
│   ├── placement_run.py      # Placement run folders, prompts and progress (krt_placement/)
│   ├── ai_backend.py         # Agent CLI backend selection (Claude Code / opencode)
│   ├── board_swaps.py        # Shared board pad/net swap helpers
│   ├── deps_check.py         # Plugin dependency checks
│   ├── about_tab.py          # About tab with version info
│   ├── gui_utils.py          # Shared GUI utilities
│   └── settings_persistence.py  # Save/restore dialog settings between sessions
├── build_router.py           # Rust module build script (--clean to remove artifacts)
├── install_plugin.py         # Plugin installer script
├── check_complete.py         # Is this board DONE? One fail-closed verdict
├── krt_registry.py           # Every runnable tool in the clone, its purpose and kind
├── krt_capabilities.py       # What this clone can do, as JSON (also route.py --capabilities)
├── package_pcm.py            # Build the KiCad PCM zip (maintainers)
├── requirements.txt          # Python dependencies
├── kicad_files/              # Example and test boards
├── docs/                     # Documentation
└── .claude/skills/           # Claude Code skills
    ├── analyze-power-nets/   # AI-powered power net analysis skill
    ├── find-high-speed-nets/ # AI-powered high-speed net identification skill
    ├── plan-pcb-routing/     # AI-powered routing plan generation skill (orchestrates the others)
    ├── identify-diff-pairs/  # Datasheet-based diff pair detection skill
    ├── recommend-stackup/    # Stackup review/recommendation skill
    ├── recommend-plane-mappings/  # Net-to-plane-layer assignment skill
    ├── diagnose-routing-failures/  # Failure root-cause and retry skill
    ├── plan-pcb-placement/   # Place by function, fast-route seeds, keep the best, route; one verifier, report
    ├── review-routed-board/  # Post-route QA and sign-off skill
    └── stress-test-router/   # Batch stress-test on real-world boards + issue filing (dev/QA)
```

## Module Overview

One-line summaries below (all of these modules live in `py_router/`); the
[Python API documentation](docs/python-api.md) has full per-module references
(signatures, dataclass fields, gotchas) with runnable examples.

### Core Routing

| Module | Purpose |
|--------|---------|
| `route.py` | CLI for single-ended routing |
| `route_diff.py` | CLI for differential pair routing |
| `route_planes.py` | CLI for power/ground plane pours (#562 bare pour), thermal via arrays, stitching and GND return vias |
| `repair_planes.py` | CLI for repairing disconnected plane regions on a board routed outside the chain (route.py's in-run plane finalize runs the same engine) |
| `routing_config.py` | Configuration classes (`GridRouteConfig`, `GridCoord`, `DiffPairNet`) |
| `routing_defaults.py` | Every default routing parameter, in one place (`FAB_TIER`, `ESCALATION`, `CLEARANCE`, ...) |
| `design_rules.py` | KiCad design rules resolved in KiCad's own order (#530): pad overrides, net classes, `.kicad_dru` rules, Board Setup minimums |
| `kicad_dru.py` | Per-layer clearance rules from the board's `.kicad_dru` (#498) |
| `fab_tiers.py` | Fab-capability floors (`--fab-tier`) and the escalation policy (`--escalation`) |
| `routing_state.py` | `RoutingState` class tracking progress, results, and PCB modifications |
| `routing_context.py` | Helper functions for building obstacles and recording success |
| `routing_common.py` | Shared utilities for route.py and route_diff.py (BGA zones, net resolution, length matching) |
| `routing_utils.py` | Shared utilities (`build_layer_map`, `iter_pad_blocked_cells`) |
| `obstacle_map.py` | Obstacle map building from PCB data |
| `obstacle_cache.py` | Net obstacle caching for incremental obstacle map builds |
| `obstacle_costs.py` | Stub and track proximity cost calculations |
| `sense_branch.py` | Protected Kelvin sense branches (#1279), declared by a KiCad group named `sense:<REF>.<PAD>` (the join pad): the member copper and its sense pads are foreign to their own net except on the join pad, so new copper joins the branch only there |
| `net_keepouts.py` | Net-filtered copper keep-outs from the board's `.kicad_dru` (`disallow` rules on a named rule area): the regions, stamped into the obstacle map only while a net a rule binds routes, and the audit of bound-net copper the shipped board has inside one |
| `area_clearance.py` | Clearance and track-width rules scoped by a rule area (`A.insideArea('ROOM')`), routed to as KiCad binds them, per item: the regions, the composition of every keep-out stamp over them (class values outside an area, the rule's value inside), the pair reading the post-route passes share, the split of a track where it leaves a tightened area, and the necking of a track where it needs a room's width |
| `keep_away.py` | Pairwise keep-away between net groups (#1146): the per-net band cost and the in-band report; the design brief's `keep_away` rules, read for the router and the placement grade alike (#1253) |
| `bresenham_utils.py` | Bresenham line-walking utilities for grid-based segment operations |
| `geometry_utils.py` | Shared geometry calculations (point-to-segment distance, segment intersection, UnionFind) |
| `routing_constants.py` | Shared constants (default layer stack, power net patterns, tolerances) |
| `terminal_colors.py` | ANSI color codes for terminal output |

### Routing Loops

| Module | Purpose |
|--------|---------|
| `diff_pair_loop.py` | Main loop for routing differential pairs |
| `single_ended_loop.py` | Main loop for routing single-ended nets |
| `reroute_loop.py` | Processes reroute queue for failed routes |
| `phase3_routing.py` | Phase 3 multi-point tap routing (connects remaining pads after length matching) |
| `diff_pair_routing.py` | Differential pair A* with centerline + offset and GND vias |
| `diff_pair_multipoint.py` | Multi-point and hybrid (coupled middle + single-ended legs) differential pairs |
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
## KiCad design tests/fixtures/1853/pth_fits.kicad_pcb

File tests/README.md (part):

# Tests

This directory holds the repo's tests: about 770 standalone `test_*.py`
scripts (unit tests and CLI/board integration chains), the runner that drives
them (`run_all.py`), the GUI/CLI parity gates (`gui_parity/`, see
[its README](gui_parity/README.md)), checked-in fixtures (`fixtures/`), the
mutation batteries (`mutate_*.py`) and the real-world stress harness
(`stress/`).

## Running Tests

Every test is a plain script. Run one from the project root or from the tests
directory:

```bash
# From project root
python3 tests/test_fanout_and_route.py --all

# From tests directory
cd tests
python3 test_fanout_and_route.py --all
```

## Running the WHOLE suite

```bash
python3 tests/run_all.py                     # everything, 4 at a time, locally
python3 tests/run_all.py --fast              # unit only (skip CLI/board tests)
python3 tests/run_all.py 908                 # only files whose name contains "908"
python3 tests/run_all.py --list              # what would run, and its classification
python3 tests/run_all.py --shard 3/50        # one of 50 duration-balanced slices (0-based)
```

`--timeout S` is the per-test budget (default 600 s; a test may declare more,
see "Writing a test" below), `-j N` the parallelism (default 4, `1` = serial),
`--shard-by stride` splits by name instead of by measured time, and
`--durations-out FILE` writes each test's wall seconds. A test is
*integration* (skipped by `--fast`) when its source imports `run_utils` or uses
`subprocess`. Each test runs with `TMPDIR`/`TEMP`/`TMP` pointed at a scratch
dir of its own, removed when it ends; run a test directly to keep its temp
output.

The summary keeps four buckets apart: passed, failed, **timed out** (a
machine-speed fact, re-run it alone before calling it a failure, though it
still makes the exit non-zero) and **self-skipped** (exit 77 with a `SKIP:`
line: the test asserted nothing, and it is never counted as a pass).

### ...on Modal, fanned out

The suite is about 770 files and, last measured, roughly 40 minutes of one
laptop. `--shard I/N` splits it into N disjoint slices, and the Modal driver
runs them in parallel containers, so a full run takes about as long as its
slowest shard:

```bash
modal run tests/stress/modal_suite/run_all_modal.py               # 50 shards
modal run tests/stress/modal_suite/run_all_modal.py --shards 25
modal run tests/stress/modal_suite/run_all_modal.py --fast        # unit lane only
modal run tests/stress/modal_suite/run_all_modal.py --filters "908 910"  # those families
```

Its other options: `--timeout` (per test, default 1000), `--jobs` (per
container, default 2), `--out-dir DIR` (every shard's log; default a temp dir,
printed), and `--write-durations` (below), which `--force-durations` lets
write from a red run.

Three things to know before you trust its output:

- **`run_all.py --shard` does the splitting**, so discovery and classification
  have ONE source of truth -- the driver never globs `test_*.py` itself. A
  local run and a 50-way fan-out therefore cover the same set. The slices are
  packed longest-first onto the least-loaded shard from the measured wall
  seconds in `tests/run_all_durations.json` (a new test is priced at the
  median of its kind; with no table it falls back to a strided split by
  name). `--write-durations` refreshes the table from a GREEN run; commit it
  when the suite's cost shape has moved. Each shard's banner says whether it
  was balanced, and on how many measured tests. No balancing beats the
  slowest single test, so a test of independent rows may declare
  `RUN_ALL_PARTS = N` and take `--part I/N`: it then runs as N units
  (`test_x.py[3/8]`), each sharded on its own.
- **The verdict is each shard's own exit code**, never the parsed counts. A
  container that OOMs prints no summary line at all, and a driver that decided
  on parsed counts would read that silence as zero failures. A shard that
  never reported fails the run and is named.
- **THIS image -- the SUITE image -- has no KiCad**, so every test needing
  pcbnew/wx self-skips (exit 77). Those are reported in their own bucket and
  are *not* passes -- and the wx/pcbnew parity gates in `tests/gui_parity/`
  are not collected by `run_all` at all, so they still need a local
  KiCad-python session.

  **Do not read that as "the cloud has no KiCad".** It is true of
  `modal_suite/run_all_modal.py` (plain `debian_slim`, no switch) and of
  nothing else. The STRESS app has carried KiCad since 2026-08-23:
  `cloud_replay_sets.py` passes `--with-kicad` **by default**
  (`--no-kicad` opts out), which sets `KICAD_SWEEP_WITH_KICAD=1` and builds
  `modal_sweep/modal_app.py` on `kicad/kicad:10.0.6`, proving `import pcbnew`
  and `kicad-cli version` during the image build so a missing binding kills
  the BUILD rather than quietly deadening the oracle legs. Note the two
  defaults differ: `modal_app.py` read on its own defaults the env var OFF,
  while the CLI you actually launch defaults it ON, and a KiCad wave labels
  itself `-kc` (`-kc-<tag>` when `KICAD_SWEEP_KICAD_IMAGE` picks another
  image).

  The suite image's self-skips have three different reasons, so read each
  `SKIP:` line rather than assuming:
  - **No KiCad.** Eight would be recovered by giving the suite image KiCad:
    `test_910_fill_for_delivery`, the two `test_1279_*_pcbnew` tests and
    `test_1450_chamfered_pad_pcbnew` (each wants KiCad's bundled python), and three that run a pcbnew/wx half under
    KiCad's python and self-skip without one (found reviewing #1272: such a
    half used to print a skip and pass, so it ran nowhere):
    `test_505_min_connection_clamp`, `test_505_gui_half_runs` and
    `test_engine_kwarg_parity_launch`. An eighth needs kicad-cli rather than
    KiCad's python: `test_1449_inrun_edge_floor` routes on every host, but
    its oracle half -- KiCad's refill at the pinned edge -- runs only with
    kicad-cli, and without it the file exits 77 (#1643).
  - **No `ortools`** (a local Python only). The `test_622_*` tests that plan
    with CP-SAT skip without it. `requirements.txt` lists it -- the bus step
    needs it (#1355) -- so the suite image installs it and runs them.

The image is a clean checkout of HEAD (reproducible, and you can keep editing
while it runs); `KICAD_SWEEP_DIRTY=1` ships the working tree instead and stamps
the provenance `+dirty`.

**The image has to be a FAITHFUL checkout, and that is harder than it looks.**
The first full cloud run reported 15 failures that all pass locally. None was a
code defect; every one was the image differing from a real working copy. They
are listed here because each is a trap that will come back:

| what was missing | what it broke |
|---|---|
| a git **index** | `run_utils.corpus_boards()` asks `git ls-files`, and `git archive` ships no `.git`, so it returned `[]` and 9 corpus-walking tests graded an EMPTY corpus instead of skipping |
| `Pillow` | `startup_checks.check_render_dependencies` raised; 3 render tests died |
| `pytest` | 2 tests imported it for fixtures (a test-only dep, correctly absent from `requirements.txt`). No test needs it now, so the image no longer installs it |
| the right **Python version** | 2 tests behave differently on 3.12 vs 3.13+ |

Three of those deserve spelling out:

- **Runtime deps come from `requirements.txt`**, never a hand-copied list. The
  sweep and route images pin numpy/scipy/shapely because that is the whole
  dependency set of the *routing* path; the suite is not that narrow.
- **The index is rebuilt from `git ls-files`, with `--force`** -- NOT
  `git add -A`. `add` honours `.gitignore`, and a file added before a matching
  rule stays tracked forever, so `-A` silently drops
  `kicad_files/interf_u_unrouted.kicad_pcb` and leaves 21 of 22 boards. The
  build asserts the count against the one measured on the host, so a short
  corpus fails the build instead of quietly shrinking what the tests grade.
- **The container's Python matches the interpreter you launched with.** This
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
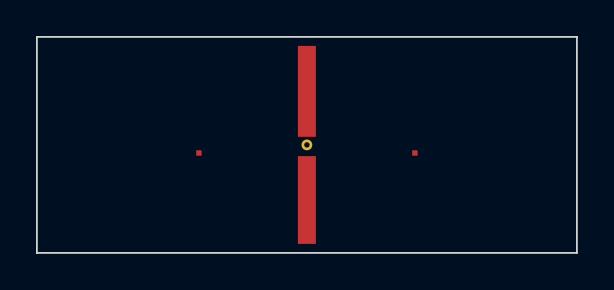
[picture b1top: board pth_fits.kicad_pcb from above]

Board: 4 copper layers, 30.0 x 12.0 mm, 3 parts (0 on the bottom side), 2 nets, no tracks yet.

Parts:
H1: H1
P1: P1
W1: W1

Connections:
SIG: P1.1, P1.2
WALL: W1.1, W1.2

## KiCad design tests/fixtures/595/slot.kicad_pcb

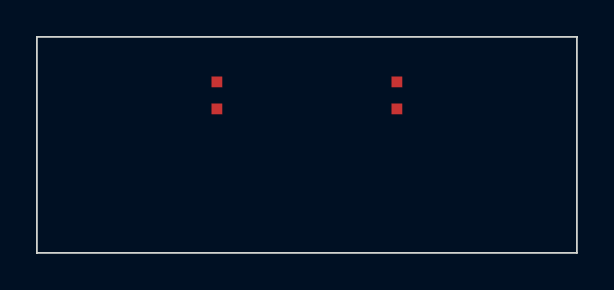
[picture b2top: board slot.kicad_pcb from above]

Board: 4 copper layers, 30.0 x 12.0 mm, 4 parts (0 on the bottom side), 2 nets, no tracks yet.

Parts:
P1: P1
P2: P2
P3: P3
P4: P4

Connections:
SIG: P1.1, P2.1
SLOW: P3.1, P4.1

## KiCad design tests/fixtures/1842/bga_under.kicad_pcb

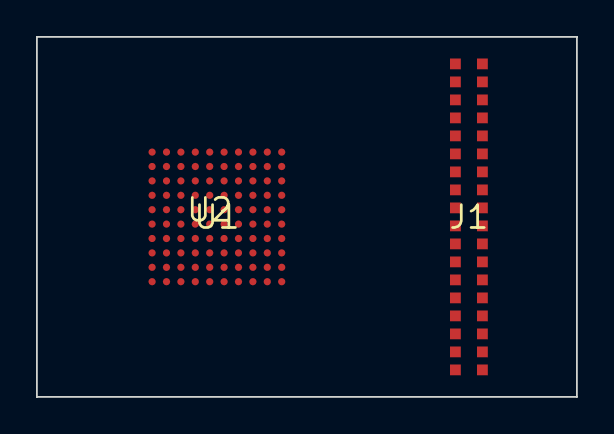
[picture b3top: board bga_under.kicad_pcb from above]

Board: 8 copper layers, 30.0 x 20.0 mm, 3 parts (1 on the bottom side), 37 nets, no tracks yet.

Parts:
J1: J1
U1: U1
U2: U2

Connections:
GND: U2.1, U2.2, U2.3, U2.4, U2.5, U2.6, U2.7, U2.8, U2.9, U2.10, U2.11, U2.12, U2.13, U2.14, U2.15, U2.16, U2.17, U2.18, U2.19, U2.20, U2.21, U2.22, U2.23, U2.24, U2.25, U2.26, U2.27, U2.28, U2.29, U2.30, U2.31, U2.32, U2.33, U2.34, U2.35, U2.36, U2.37, U2.38, U2.39, U2.40, U2.41, U2.42, U2.43, U2.44, U2.45, U2.46, U2.47, U2.48, U2.49, U2.50, U2.51, U2.52, U2.53, U2.54, U2.55, U2.56, U2.57, U2.58, U2.59, U2.60, U2.61, U2.62, U2.63, U2.64, U2.65, U2.66, U2.67, U2.68, U2.69, U2.70, U2.71, U2.72, U2.73, U2.74, U2.75, U2.76, U2.77, U2.78, U2.79, U2.80, U2.81
S01: J1.1, U1.C3
S02: J1.2, U1.C4
S03: J1.3, U1.C5
S04: J1.4, U1.C6
S05: J1.5, U1.C7
S06: J1.6, U1.C8
S07: J1.7, U1.D3
S08: J1.8, U1.D4
S09: J1.9, U1.D5
S10: J1.10, U1.D6
S11: J1.11, U1.D7
S12: J1.12, U1.D8
S13: J1.13, U1.E3
S14: J1.14, U1.E4
S15: J1.15, U1.E5
S16: J1.16, U1.E6
S17: J1.17, U1.E7
S18: J1.18, U1.E8
S19: J1.19, U1.F3
S20: J1.20, U1.F4
S21: J1.21, U1.F5
S22: J1.22, U1.F6
S23: J1.23, U1.F7
S24: J1.24, U1.F8
S25: J1.25, U1.G3
S26: J1.26, U1.G4
S27: J1.27, U1.G5
S28: J1.28, U1.G6
S29: J1.29, U1.G7
S30: J1.30, U1.G8
S31: J1.31, U1.H3
S32: J1.32, U1.H4
S33: J1.33, U1.H5
S34: J1.34, U1.H6
S35: J1.35, U1.H7
S36: J1.36, U1.H8

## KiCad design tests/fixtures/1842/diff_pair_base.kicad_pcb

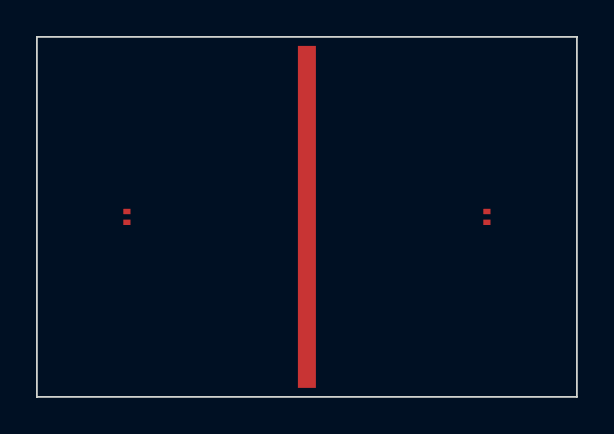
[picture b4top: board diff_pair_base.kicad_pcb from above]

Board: 8 copper layers, 30.0 x 20.0 mm, 4 parts (0 on the bottom side), 2 nets, no tracks yet.

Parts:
J1: J1
J2: J2
U9: U9
W1: W1

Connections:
/D0_N: J1.2, J2.2
/D0_P: J1.1, J2.1
